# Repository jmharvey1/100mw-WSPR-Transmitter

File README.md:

# 100mw-WSPR-Transmitter
Material Needed to Replicate the 100mw Transmitter shown in the YouTube Video 
The Video can be seen here: https://youtu.be/ck376xusUuw

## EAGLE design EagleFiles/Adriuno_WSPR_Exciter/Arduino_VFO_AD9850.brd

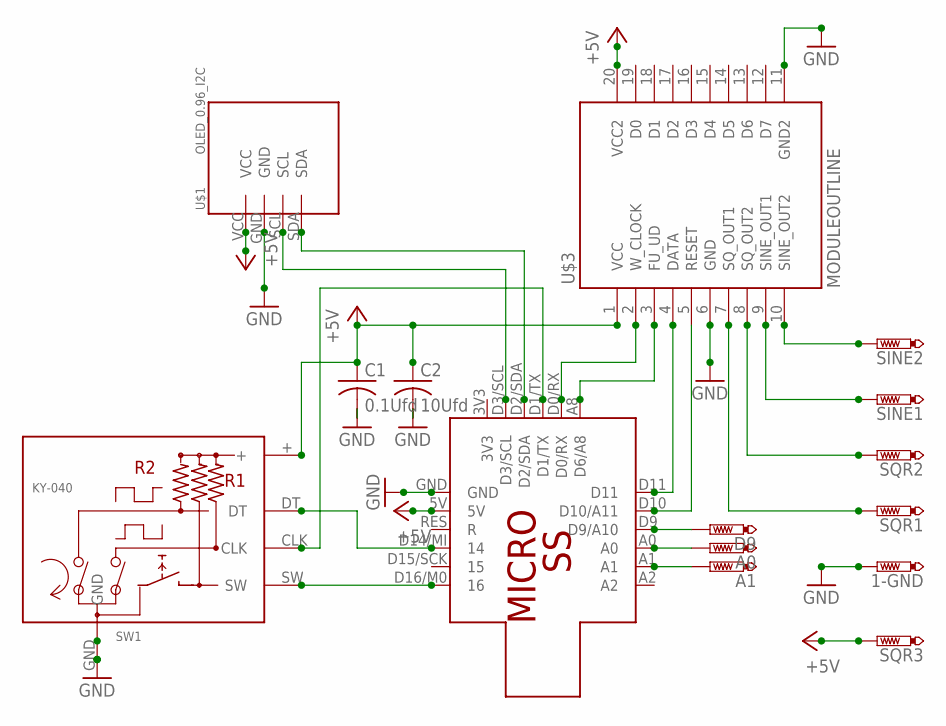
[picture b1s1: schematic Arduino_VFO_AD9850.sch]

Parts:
1-GND: 1 - GND; P1-20Y
A0, A1: 1 - GND; P1-20Y
C1: 0.1Ufd; C050-024X044
C2: 10Ufd; C050-024X044
D9: 1 - GND; P1-20Y
SINE1: 1 - GND; P1-20Y
SINE2: SINE2; P1-20Y
SQR1, SQR2, SQR3: 1 - GND; P1-20Y
SW1: KY-040; KY040
U$1: OLED_0.96_I2C
U$3: MODULEOUTLINE; MODULE_OUTLINE
U$4: SS_MICRO

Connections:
+5V: C1.1, C2.1, SQR3.TP, SW1.+, U$1.VCC, U$3.1 (VCC), U$3.20 (VCC2), U$4.5V
GND: 1-GND.TP, C1.2, C2.2, SW1.GND, U$1.GND, U$3.6 (GND), U$3.11 (GND2), U$4.GND
unnamed: U$1.SDA, U$4.D2/SDA
unnamed: U$1.SCL, U$4.D3/SCL
unnamed: SW1.CLK, U$4.D1/TX
unnamed: U$3.2 (W_CLOCK), U$4.D0/RX
unnamed: U$3.4 (DATA), U$4.D11
unnamed: U$3.5 (RESET), U$4.D10 (D10/A11)
unnamed: SW1.DT, U$4.D14/MI (14)
unnamed: SW1.SW, U$4.D16/M0 (16)
unnamed: SINE2.TP, U$3.10 (SINE_OUT2)
unnamed: SINE1.TP, U$3.9 (SINE_OUT1)
unnamed: SQR2.TP, U$3.8 (SQ_OUT2)
unnamed: SQR1.TP, U$3.7 (SQ_OUT1)
unnamed: D9.TP, U$4.D9 (D9/A10)
unnamed: A0.TP, U$4.A0
unnamed: A1.TP, U$4.A1
unnamed: U$3.3 (FU_UD), U$4.A8 (D6/A8)

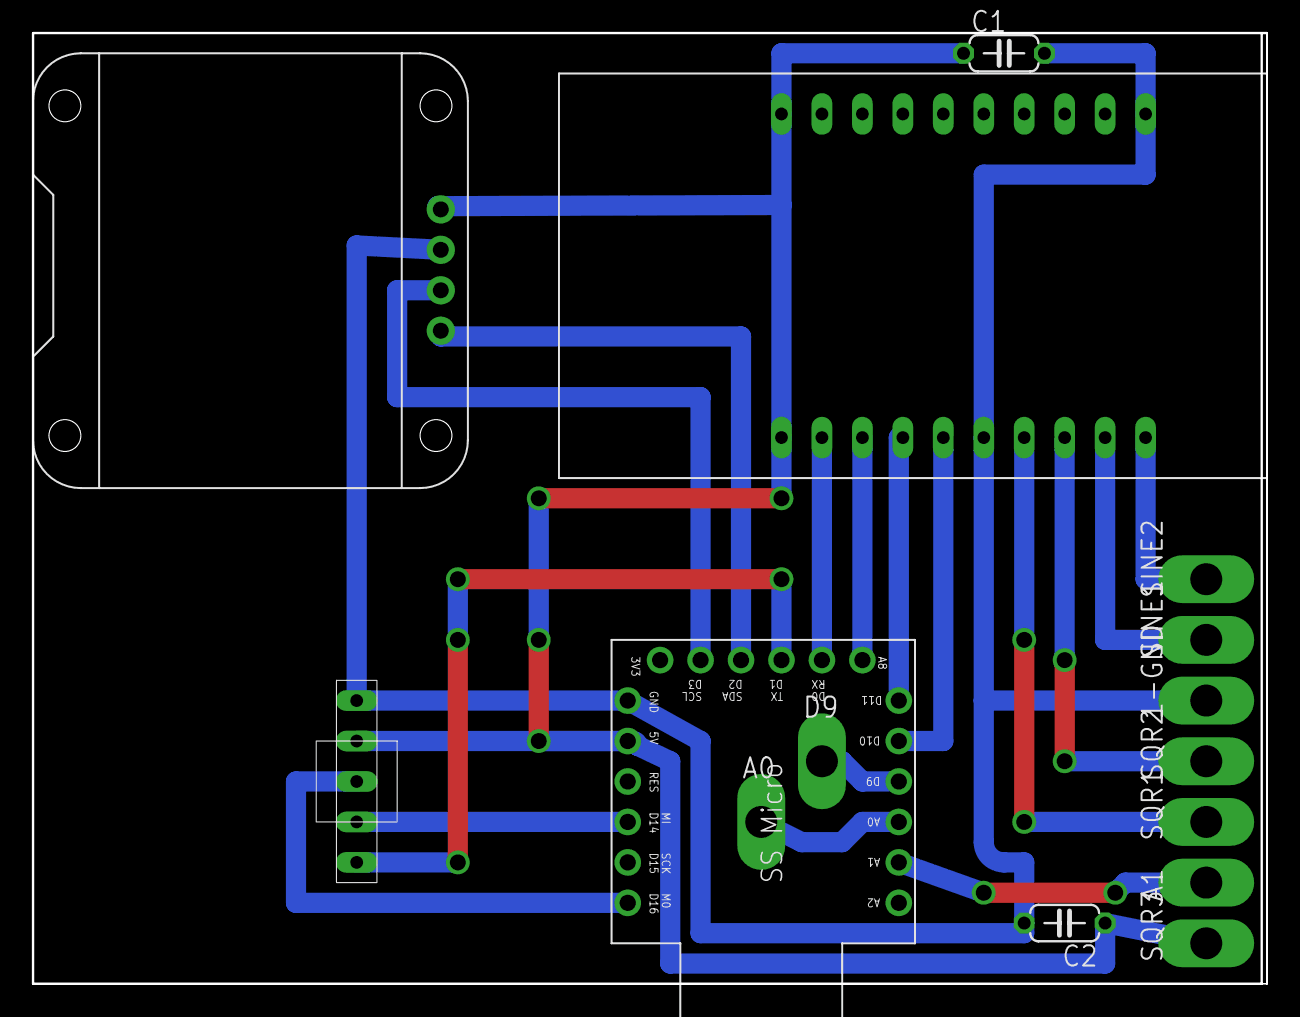
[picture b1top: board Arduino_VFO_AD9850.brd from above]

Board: 2 copper layers, 77.5 x 59.7 mm, 15 parts (0 on the bottom side), 18 nets.

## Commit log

2017-06-10 Added initial files
    Basic files used to build the 100mw WSPR transmitter shown in the video
2017-06-10 Re-Arranged File Layout
    Moved Arduino Sketch/Folder under Arduino Folder
2017-06-10 Added YouTube Hyper Link
    Added YouTube Hyper Link
2018-03-09 Added Notes/Comments for UNO based interface
    In addtion to comments for using an UNO type Arduino, changed the D and
    S arrays from interger to byte type to conserve SRAM space
2018-03-10 Added coil build instructions for the 100mw Amplifier
    See text file found st EagleFiles\100mwAmp\CoilBuildInstructions.txt
2018-03-16 Added 20 Mtrs to Option Pick List
    Also added Coil data for 20 meter low pass filter to Coil Build
    Instructiion text file
